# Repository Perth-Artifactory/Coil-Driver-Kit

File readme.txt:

This is the MASTER version of the coil driver circuit, this is the version that should be electrically sound and functional however it has not been
rigourously tested in the real world, please use the STABLE version if you want something you know will work, otherwise happy hacking!

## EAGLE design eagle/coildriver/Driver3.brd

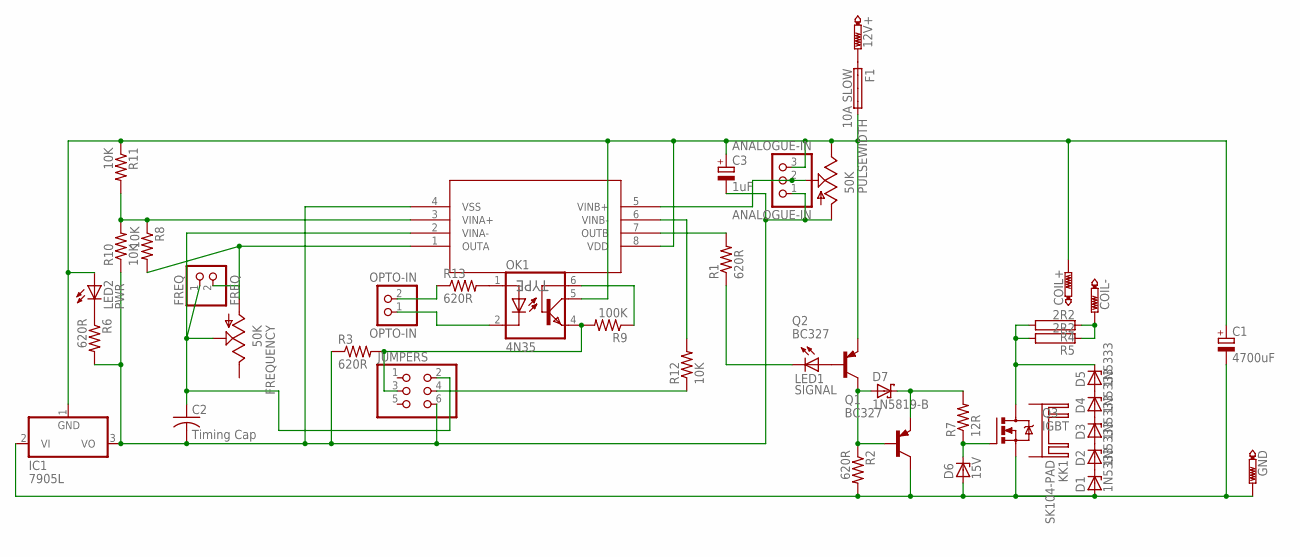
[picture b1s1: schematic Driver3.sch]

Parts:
12V+: PTR1PAD1-20Y; P1-20Y
ANALOGUE-IN: ANALOGUE-IN; 1X03
C1: 4700uF; E7,5-16
C2: Timing Cap; C050-025X075
C3: 1uF; E5-5
COIL+: PTR1PAD1-20Y; P1-20Y
COIL-: PTR1PAD1-20Y; P1-20Y
D1, D2, D3, D4, D5: 1N5333; C1702-15
D6: 15V; DO34Z7
D7: 1N5819-B; DO41-7.6
F1: 10A SLOW; SHK20L
FREQ: FREQ; 1X02
FREQUENCY: 50K; B25X
GND: PTR1PAD1-20Y; P1-20Y
IC1: 7905L; TO92
JUMPERS: PINHD-2X3; 2X03
KK1: SK104-PAD
LED1: SIGNAL; LED3MM
LED2: PWR; LED3MM
OK1: 4N35; DIL06
OPTO-IN: OPTO-IN; 1X02
PULSEWIDTH: 50K; B25X
Q1, Q2: BC327; TO92
Q3: IGBT; TO220BV
R1, R2, R3, R6, R13: 620R; 0204/7
R4, R5: 2R2; HPS947
R7: 12R; 0204/7
R8, R10, R11, R12: 10K; 0204/7
R9: 100K; 0204/7
U$1: MCP6542-X/P; PDIP8_300MC

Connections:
unnamed: D6.C, Q3.G, R7.1
unnamed: COIL-.TP, R4.1, R5.1
unnamed: D7.A, Q1.2 (B), Q2.3 (C), R2.1
unnamed: ANALOGUE-IN.3, C1.+, C3.+, COIL+.TP, F1.2A, IC1.1 (GND), LED2.A, OK1.5 (COL), PULSEWIDTH.E, Q2.1 (E), R11.1, U$1.8 (VDD)
unnamed: R8.1, R10.2, R11.2, U$1.3 (VINA+)
unnamed: D4.C, D5.A
unnamed: R1.2, U$1.7 (OUTB)
unnamed: C1.-, D1.A, D6.A, GND.TP, IC1.2 (VI), Q1.3 (C), Q3.S, R2.2
unnamed: ANALOGUE-IN.1, C2.2, C3.-, IC1.3 (VO), JUMPERS.6, PULSEWIDTH.A, R3.1, R6.2, R10.1, U$1.4 (VSS)
unnamed: D1.C, D2.A
unnamed: D2.C, D3.A
unnamed: D3.C, D4.A
unnamed: D5.C, Q3.D, R4.2, R5.2
unnamed: 12V+.TP, F1.1A
unnamed: LED1.A, Q2.2 (B)
unnamed: ANALOGUE-IN.2, PULSEWIDTH.S, U$1.5 (VINB+)
unnamed: LED2.K (C), R6.1
unnamed: D7.C, Q1.1 (E), R7.2
unnamed: R12.2, U$1.6 (VINB-)
unnamed: FREQ.2, FREQUENCY.A, R8.2, U$1.1 (OUTA)
unnamed: C2.1, FREQ.1, FREQUENCY.S, JUMPERS.2, U$1.2 (VINA-)
unnamed: JUMPERS.4, R12.1
unnamed: JUMPERS.3, OK1.4 (EMI), R3.2, R9.2
unnamed: OK1.6 (BAS), R9.1
unnamed: OK1.1 (A), R13.2
unnamed: OK1.2 (C), OPTO-IN.1
unnamed: OPTO-IN.2, R13.1
unnamed: LED1.K (C), R1.1

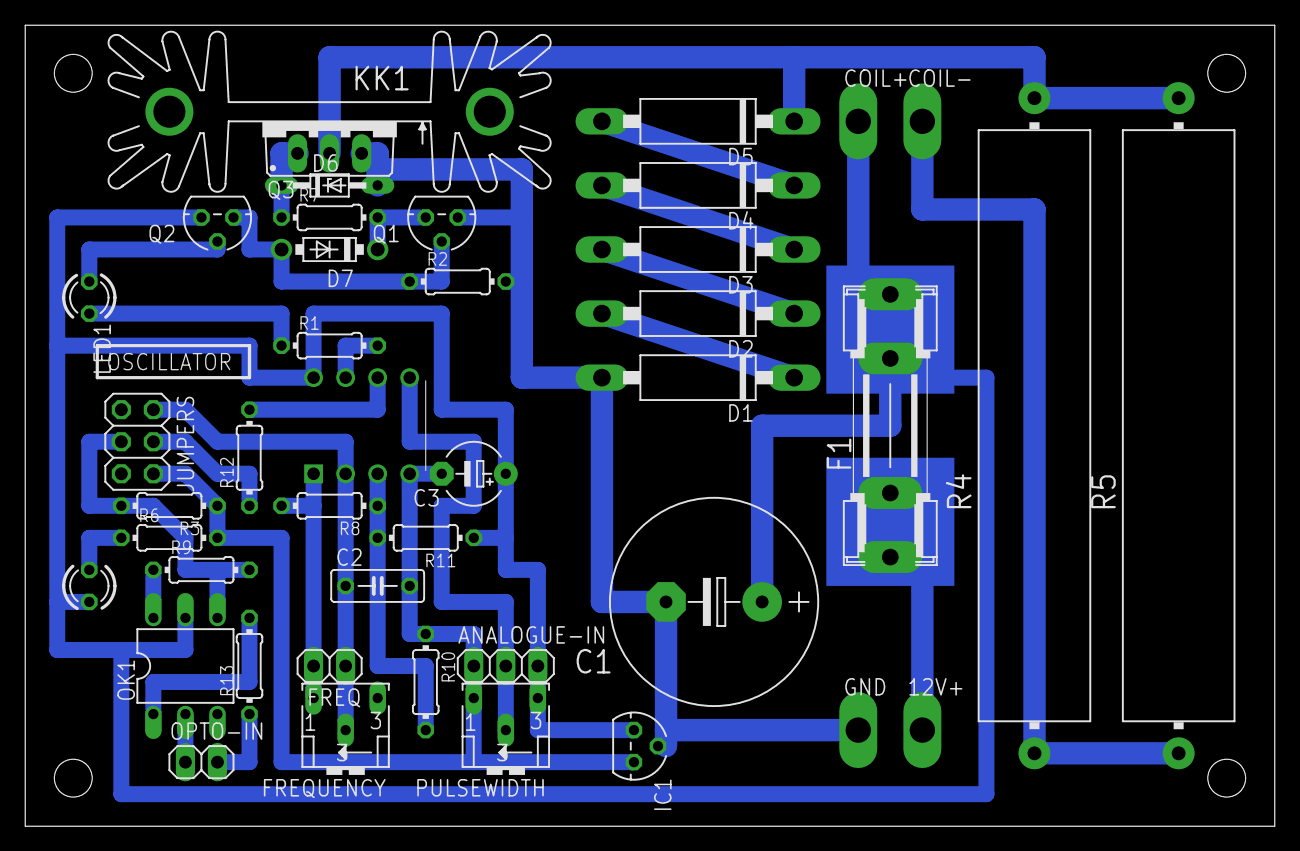
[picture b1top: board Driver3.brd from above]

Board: 2 copper layers, 99.1 x 63.5 mm, 43 parts (0 on the bottom side), 28 nets.

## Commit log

2011-07-09 Removed superfluous folders inherited from my dropbox
2011-07-15 Added documentation
2011-08-22 Implemented comparator based oscillator in schematic, still needs laying out
2011-08-27 Started migration to v2.0 driver using comparator oscillator
2011-08-30 wired oscillator, needs signal LED and minimum resistor on frequency pot.
2011-08-30 better break-in for signal and oscillator select
2011-08-31 one break-in/out point for all signals, corrected voltage rail errors in comparator
2011-08-31 different headers, added opto-coupler
2011-08-31 Wired in signal LED
2011-08-31 Renamed TTL LED to signal LED
2011-08-31 Fixed incorrect polarity on signal LED
2011-08-31 went to town with the layout
2011-09-01 more layout edits
2011-09-04 Did some minor layouting and cleanup, layout *should* now be workable for prototyping
2011-09-04 jumper correction
2011-09-04 finished wiring
2011-09-04 checked for layout errors, ready to prototype
2011-09-04 Board slightly enlarged, all one layer no jumpers.
2011-09-04 Added readme.txt for experimental branch and branched to experimental
2011-09-05 Rerouted ref bus for oscillator around the bottom of the board and shifted circuit over to allow clearance for mounting holes.
2011-09-07 Moved current version from experimental to master
2011-09-07 Minor layouting fixes, improved spacing between potentiometers
2011-09-08 Silkscreen cleanup and minor layouting changes, aesthetic only.
2011-09-08 Fixed some ERC errors introduced from tweaking the layout
2011-09-12 Fixed screw terminal hole spacing, added heatsink mounting holes and general silkscreen cleanup
2011-09-17 Silkscreen improvements and added heatsink
2011-09-17 IMPORTANT! fix on comparator polarity
2011-09-17 swapped comp gates and laid out copper, needs cleanup
2011-09-17 Silkscreen improvements and general cleanup
2011-09-17 there was an unnecessary kink in a wire! (and other edits)
2011-09-19 Minor silkscreen tweaks and layout adjustments.
2011-09-25 just a few copper layer overlaps
2011-09-25 Minor tweaks to silkscreen, generated manufacturing files, ready to send to PCB fabricator.
2011-09-25 Resistors moved to standard pitch, more silkscreen and spacing tweaks
2011-09-25 last fixes
2011-09-25 Generated fresh Gerber files, this revision sent for fabrication.
2011-09-26 version2 instructions
2011-09-26 Remove archaic costing document, doesnt belong in VCS
2011-09-27 Updated parts list on the v2 manual
2011-09-27 Added license documents
2011-09-27 Couple of fixes to the documentation parts list
2011-10-19 New boards tested, moving to stable
2011-11-21 Updates to instructions and output at PDF
2011-11-21 Got master back in sync with stable
2011-12-24 Yay for Eagle XML format
2011-12-24 Silkscreen fixes

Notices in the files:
eagle/coildriver/Driver3.brd:
Licensed under the TAPR NCL
Copyright 2011
